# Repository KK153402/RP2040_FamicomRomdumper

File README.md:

# Famicom ROM Dumper rev2（AE-RP2040）

ファミコンカセットを USB 経由で吸い出して `.nes` ファイルに保存するダンパーの、rev2 基板用ファームウェアと PC 側スクリプト。

| 項目 | 内容 |
|---|---|
| 基板 | rev2（MCU：秋月 AE-RP2040、カート電源：TPS2051C）→ [hardware.md](hardware.md) |
| ファーム | v4.4（arduino-pico / PlatformIO） |
| PC スクリプト | `tools/dump_nes.py` v3.1（Python 3、pyserial） |
| プロトコル | [protocol.md](protocol.md) |
| 対応カセット | Mapper 0（NROM）、1（MMC1）、2（UNROM）、3（CNROM）、4（MMC3）は実機確認済み。22（VRC2a）、206（Namco 108 系）は実装のみ（未確認） |
| 実績 | スーパーマリオブラザーズ：CRC32 `D445F698`、Mesen で起動確認 |

## フォルダ構成

| パス | 内容 |
|---|---|
| `platformio.ini` | PlatformIO 設定 |
| `src/main.cpp` | ファームウェア |
| `tools/dump_nes.py` | 吸い出しスクリプト |
| `firmware.uf2` | ビルド済みファーム（ドラッグ＆ドロップ書き込み用） |
| `protocol.md` | シリアルコマンド仕様 |

---

## 1. 開発環境（PlatformIO）

1. VS Code に PlatformIO IDE 拡張を入れる
2. PIO Home → Platforms → Advanced Installation で `https://github.com/maxgerhardt/platform-raspberrypi.git` をインストール
3. このフォルダを開く（初回は toolchain 等のダウンロードに数分かかる）

`platformio.ini`：

```ini
[env:ae-rp2040]
platform = https://github.com/maxgerhardt/platform-raspberrypi.git
board = pico                      ; AE-RP2040 は Pico と同じフラッシュ(2MB)・12MHz 水晶
framework = arduino
board_build.core = earlephilhower ; arduino-pico (Earle Philhower 版)
monitor_speed = 115200            ; USB CDC なので実際の速度とは無関係

; Windows でドライバ不要にするため、RPI-RP2 ドライブへのコピー方式で書き込む
upload_protocol = mbed
upload_port = D:                  ; RPI-RP2 に割り当てられたドライブ文字
```

- `board = rpipico`（「Pico (Raspberry Pi)」）を選んだ場合は `board_build.core` の行は不要
- `platform_packages` でコアのバージョンを古いもの（2.x 等）に固定しないこと（v4.1 以降は 5.x 系で確認）
- Windows でプラットフォームのインストール時に git のエラーが出たら、管理者権限で `git config --system core.longpaths true` を実行してから再インストール

## 2. 書き込み

### 通常（Upload ボタン）

PlatformIO の **Upload（→）** を押す。ファームが動いていれば、1200 bps タッチで自動的に BOOTSEL に入り、`RPI-RP2` ドライブへ `firmware.uf2` がコピーされる。

### 初回・ファームが止まったとき

1. **BOOT を押したまま RUN を押して離し、BOOT を離す** → `RPI-RP2` ドライブが現れる
2. `firmware.uf2`（またはビルド後の `.pio/build/ae-rp2040/firmware.uf2`）を `RPI-RP2` ドライブの中にドラッグ＆ドロップ
3. ドライブが自動で消え、ファームが起動する（「取り外された」等の警告は無視してよい）
4. デバイスマネージャーの「ポート（COM と LPT）」に `USB シリアル デバイス (COMx)` が出れば成功

`RPI-RP2` ドライブは書き込み用の仮想ドライブで、コピーしたファイルは中に残らない（常に `INDEX.HTM` と `INFO_UF2.TXT` だけが見える）。

### 書き込みで出るエラー

| メッセージ | 原因 | 対処 |
|---|---|---|
| `Please specify upload_port` | 書き込み先のドライブが見つからない | `upload_port` に `RPI-RP2` のドライブ文字を指定 |
| `picotool was unable to connect. You may need to install a driver via Zadig` | 既定の picotool 方式は Windows ではドライバが必要 | `upload_protocol = mbed`（上記）にする。または Zadig で **RP2 Boot (Interface 1)** に WinUSB を入れる（**Interface 0 は選ばない**。RPI-RP2 ドライブが見えなくなる） |
| デバイスマネージャーに「RP2 Boot」（！マーク） | BOOTSEL 中の picotool 用インターフェース。ドライバ未導入なだけ | 上と同じ。mbed 方式なら無視してよい |

書き込み中・BOOTSEL 中は GPIO がすべて入力になり、基板のプル抵抗でカート電源 OFF・バス Hi-Z に固定される。カセットを挿したままでも安全。

---

## 3. 動作確認

シリアルモニタ（VS Code の Serial Monitor、Tera Term 等）で行う。ポート欄の ↻ で COM を更新して選ぶ。ボーレートは何でもよい（1200 以外）。

### 3.1 カセットなし

| 操作 | 期待値 | 確認していること |
|---|---|---|
| USB 接続 | D1（+5V）点灯 | 電源 |
| `Q` | `VCC_CART=0〜数十mV  /FLT=1  power=OFF  BUS_EN_N=1` | 起動時の安全状態 |
| `O 1` | `PWR ON vcart=4500〜5100mV`、D2（VCC_CART）・D3（STATUS）点灯 | TPS2051C、VCART_SENSE |
| `T` | 12 行すべて `OK`、最後に `LOOPBACK OK` | データバス 16 本と 595/165/U10 の経路 |
| `R` | `CPU D=FF  PPU D=FF` | プルアップ R1〜R16 |
| `G` | `CIRAM_A10=1  CIRAM_CE_N=1` | プルアップ R33/R34、U11/U12 |
| `O 0` | `PWR OFF vcart=450〜500mV`（警告なし）、D2・D3 消灯 | 放電 |

### 3.2 カセットあり

**カセットの抜き差しは必ず D2（VCC_CART）が消えている状態で行う。** 動作確認が済むまでは USB も抜いておくとより安全。

| 操作 | 期待値（スーパーマリオブラザーズ） | 確認していること |
|---|---|---|
| `O 1` | `PWR ON vcart=4900mV 前後` | カセットの消費電流で極端に下がらないか |
| `V` | `NMI $8082`、`RESET $8000`、`IRQ $FFF0`、3 行とも `[OK]` | PRG 側（CPU アドレス、/ROMSEL、M2） |
| `P FFF0 16` | `FFF0: 19 19 1A 1A 1C 1D 1D 1E 1E 1F 82 80 00 80 F0 FF` | 同上 |
| `H 0000 16` | `0000: 03 0F 1F 1F 1C 24 26 66 00 00 00 00 1F 3F 3F 7F` | CHR 側（PPU アドレス、/RD） |
| `M` | `VERTICAL (follows PA10)` | CIRAM A10 |
| `O 0` | `PWR OFF` | |

`V` が `$FFFF [NG] open bus` のときはカセットが何も出力していない（未挿入・接触不良）。

### 3.3 吸い出し

**シリアルモニタを閉じてから**実行する（COM ポートは 1 つのアプリしか開けない）。

```
python -m pip install pyserial
python tools/dump_nes.py smb.nes
```

出力例（tool v3。`xxxxxxxx` は実測値が入る）：

```
ポート: COM8   マッパー: 0 (NROM)
  PWR ON vcart=4951mV
  [1] PRG 32 KB, CHR 8 KB, mirroring V, CRC32 PRG xxxxxxxx / CHR xxxxxxxx / PRG+CHR D445F698
      所要 1.0 s（うちカセット読み出し 0.9 s）
  [2] PRG 32 KB, CHR 8 KB, mirroring V, CRC32 PRG xxxxxxxx / CHR xxxxxxxx / PRG+CHR D445F698
      所要 1.0 s（うちカセット読み出し 0.9 s）
  2回読み 合計 2.0 s
  PWR OFF vcart=466mV
保存しました: smb.nes
```

- `pip install serial` ではなく **`pyserial`**。仮想環境を使っている場合は `python -m pip` で入れる
- ファーム v4.0 以前（`B` コマンドなし）の場合は `--legacy` を付ける

### 3.4 マッパー付きカセットの吸い出し [tool v3 / fw v4.3]

カセットにはマッパー情報が書かれていないので、**NesCartDB で日本版（日の丸の行）の iNES Mapper を調べて `--mapper` で指定**する。容量（バンク数）と CHR-RAM かどうかは自動で判定する。

```
python tools/dump_nes.py dq2.nes --mapper 2
```

| `--mapper` | マッパー | 主な基板 | 検証用カセット |
|---|---|---|---|
| 0（省略可） | NROM | HVC-NROM | スーパーマリオブラザーズ（確認済み） |
| 1 | MMC1 | HVC-SxROM（SLROM、SGROM、SNROM…） | 忍者龍剣伝（HVC-SLROM） |
| 2 | UNROM | HVC-UNROM、HVC-UOROM | ドラゴンクエストII（HVC-UNROM） |
| 3 | CNROM | HVC-CNROM | ソロモンの鍵（HVC-CNROM） |
| 4 | MMC3 | HVC-TxROM（TLROM、TSROM、TGROM…） | スーパーマリオブラザーズ3（HVC-TSROM） |
| 22 | VRC2a（コナミ） | 351618 など | がんばれペナントレース |
| 206 | Namco 108 系 | NAMCOT-34xx | ドラゴンバスターII |

確認のしかた：

1. 2 回の読み出しが一致して保存されること
2. 表示される `PRG` / `CHR` / `PRG+CHR` の CRC32 が、NesCartDB の ROM Details（PRG0 / CHR0 / ROMs Combined）と一致すること。CHR-RAM のカセットは PRG だけ比べる
3. Mesen で起動すること

CRC32 が合わないときは `--banks` を付けると、PRG は 8 KB、CHR は 1 KB ごとの CRC32 も表示する。版違いか、特定のバンクだけずれているかの切り分けに使う。

| 注意 | 理由 |
|---|---|
| マッパー番号を間違えると `固定バンクと一致するバンクが見つかりません` 等で止まる | 容量判定が成立しないため。保存はされない |
| **バッテリーバックアップ付き（セーブできる）カセットは、セーブデータが消えてもよいものだけにする** | 本ツールは `$6000`〜`$7FFF`（PRG-RAM）には書かないが、抜き差し時の電源の立ち上がり・立ち下がりで消えることがある（実機と同じリスク） |
| MMC1 の PRG 512 KB（SUROM：ドラゴンクエストIV 等）、MMC3 の 4 画面基板は未対応 | バンク切替の追加ビットが必要 |

所要時間の目安（実測の PRG 18.6 µs/B、CHR 35 µs/B から計算。USB 転送とバンク切替の往復を除く）：

| カセット | 容量 | 1 回の読み出し |
|---|---|---|
| ドラゴンクエストII | PRG 128 KB | 約 2.4 s |
| 忍者龍剣伝 | PRG 128 KB + CHR 128 KB | 約 7 s |
| スーパーマリオブラザーズ3 | PRG 256 KB + CHR 128 KB | 約 9.5 s |

---

## 4. 吸い出しがうまくいかないとき

| 症状 | 考えられる原因 | 対処 |
|---|---|---|
| `RP2040 のポートが見つかりません` | ファーム未書き込み、または BOOTSEL のまま | 2. の手順で書き込む |
| `応答がありません` | シリアルモニタが開いたまま | モニタを閉じる |
| `PWR NG` | カセットの短絡・逆挿し、または USB の電源不足 | カセットを確認。USB ハブを使わず PC に直結 |
| `ERR overcurrent` | 吸い出し中に過電流（/FLT） | カセットを抜いて `Q`、`O 1` で再確認 |
| `2回のダンプが一致しません` | カセットの接触不良 | 端子を清掃。それでも NG なら `S 125 1000`（アクセス待ちを延ばす）→ `S 500 1000`（クロックを下げる） |
| `転送エラー` が再送しても直らない | USB ケーブル・ハブ | 別のケーブル、PC の別のポートで試す |

---

## 5. 変更履歴

| 版 | 内容 |
|---|---|
| tool v3.1 | マッパー 22（VRC2a）、206（Namco 108 系）を追加。`--banks`（バンクごとの CRC32 表示）を追加 |
| fw v4.4 | `B P` で `$6000`〜`$7FFF`（PRG-RAM、セーブデータ）を読めるようにした。`$8000` 未満は /ROMSEL を H のまま読む |
| fw v4.3 | MMC1 で書き込みが無視される問題を修正（`W` の前にダミー読み出しサイクルを追加） |
| fw v4.2 / tool v3 | マッパー対応（MMC1 / UNROM / CNROM / MMC3）。CPU 書き込み `W`、PPU 書き込み `X` を追加。容量・CHR-RAM の自動判定、バス競合の回避、PRG / CHR / 合計の CRC32 表示 |
| fw v4.1 / tool v2 | 高速化：SIO 直接操作＋ns 単位のタイミング（シフトクロック 4 MHz）、PRG はアドレス 16 bit・データ 8 bit だけ転送。ブロック読み出し `B`（ブロック CRC、再送）、タイミング設定 `S`（ns 単位）を追加 |
| fw v4.0 / tool v1.2 | Windows で受信データが欠ける問題を修正（`writeAll()`、pySerial の `timeout` を途中で変更しない） |
| fw v4.0 | rev2 初版。v3 を AE-RP2040 に移植。カート電源制御 `O`、状態表示 `Q`、折り返し試験 `T`、過電流監視を追加。電圧を mV 表示に。ベクタ `$FFFF` を NG 判定に |
| v3（rev1） | ESP32 版。ビットバング、115200 bps |

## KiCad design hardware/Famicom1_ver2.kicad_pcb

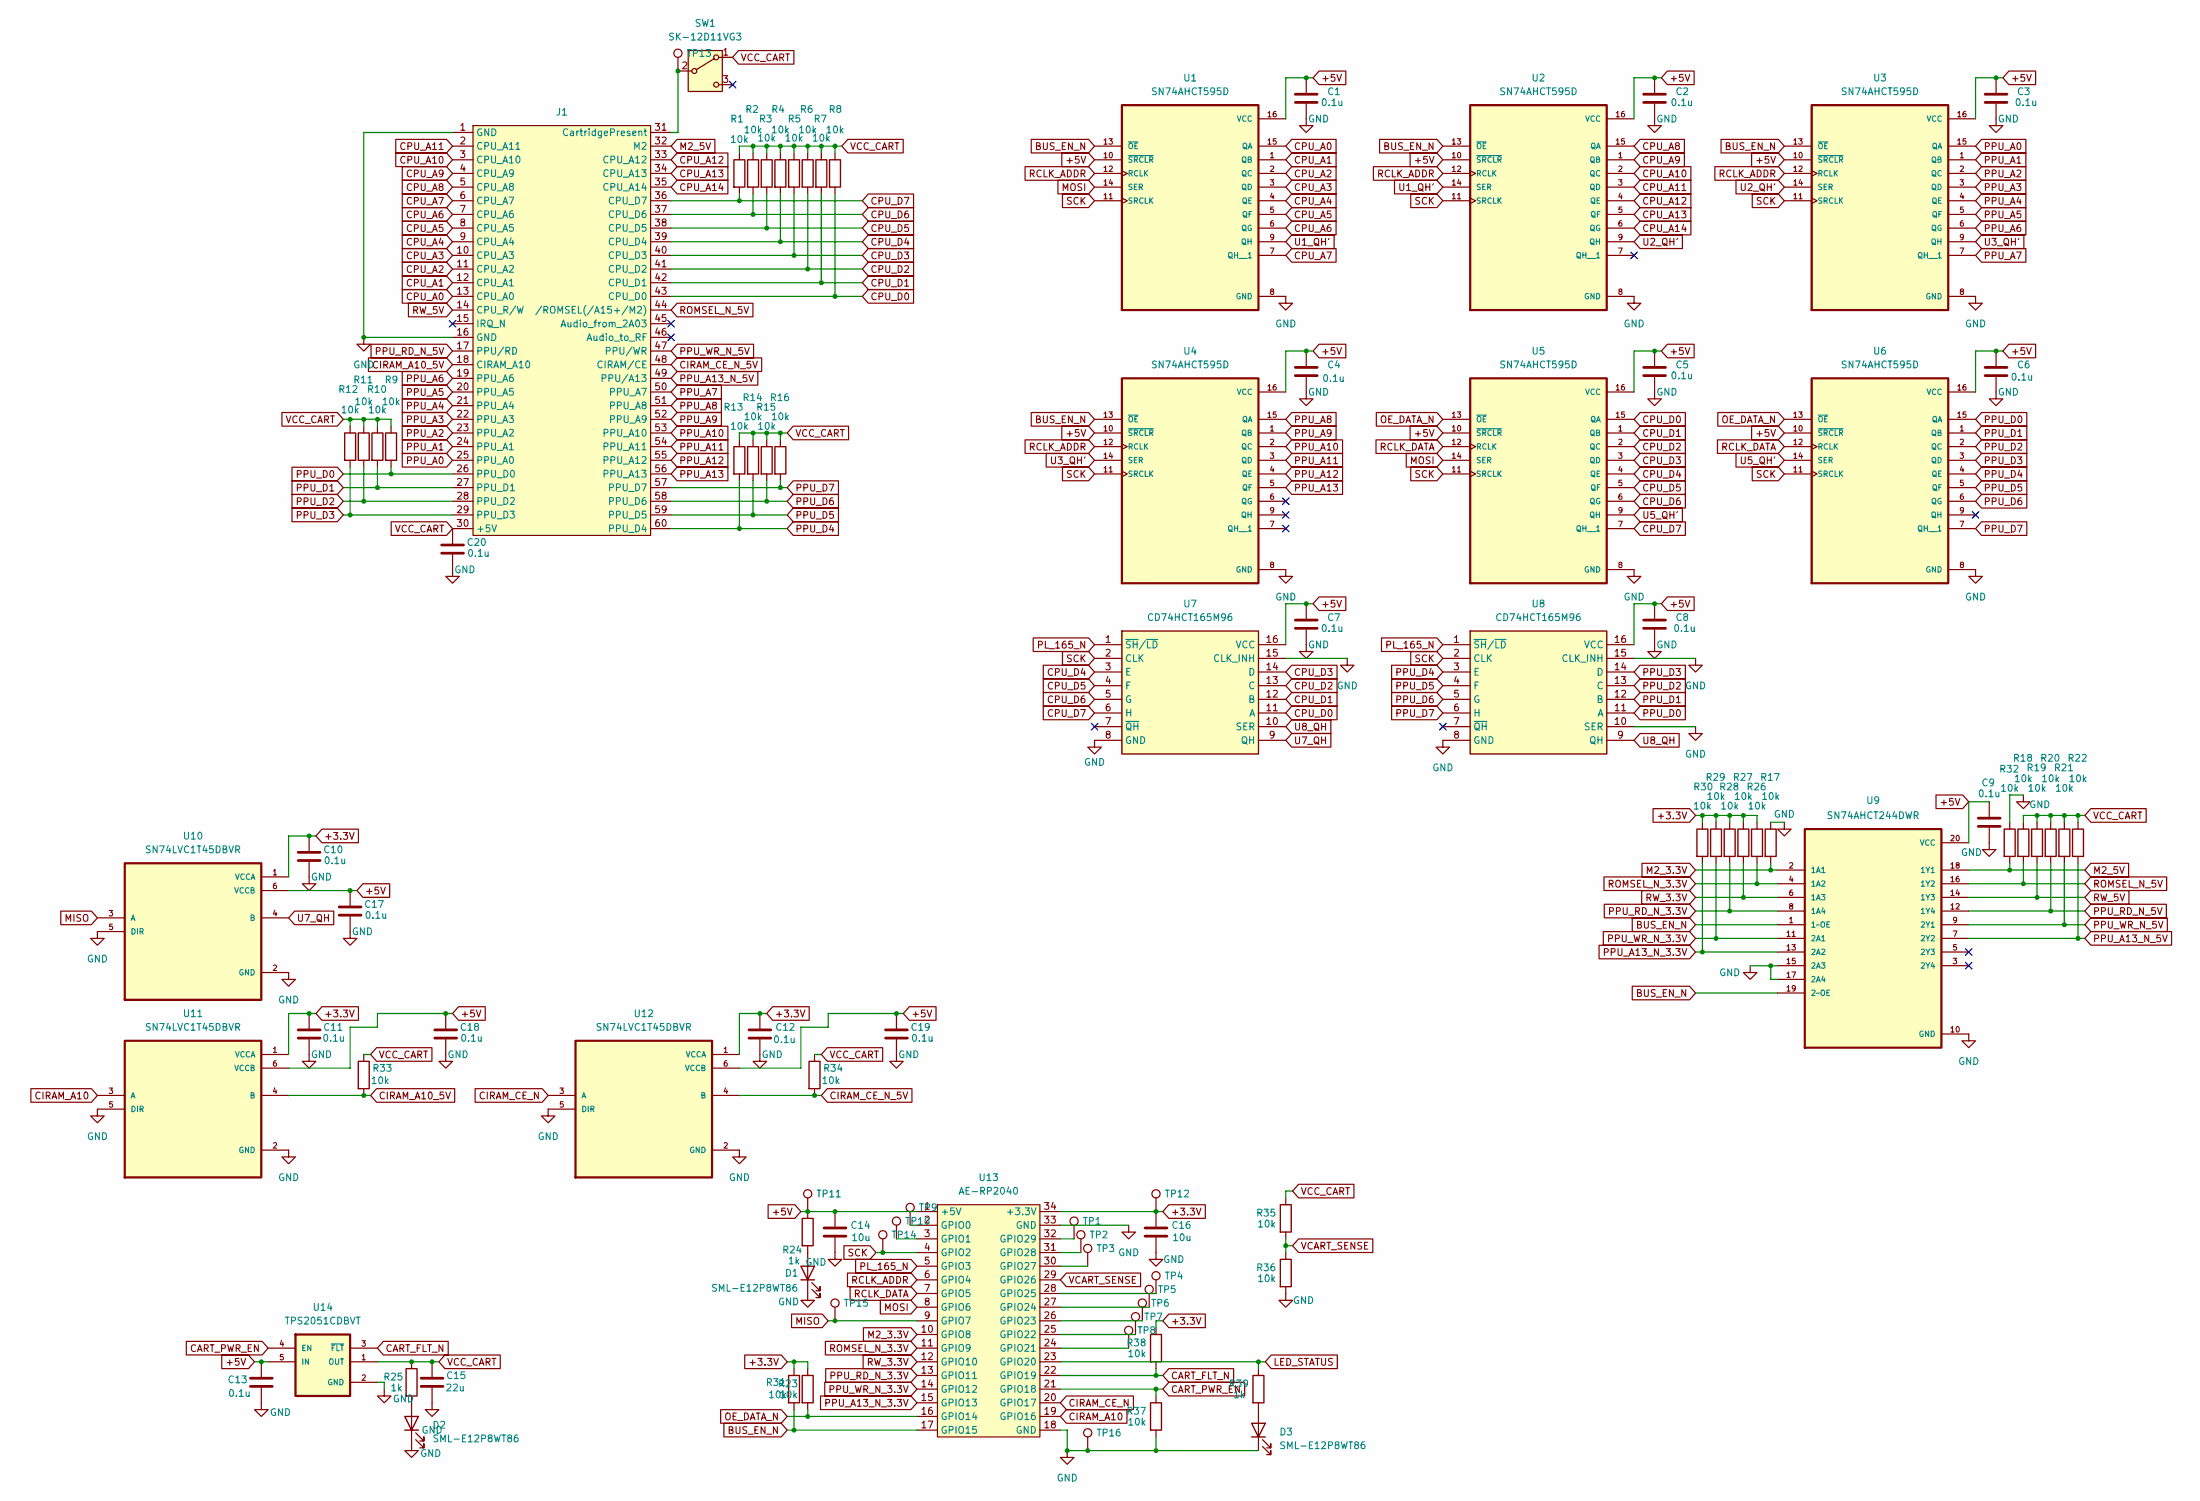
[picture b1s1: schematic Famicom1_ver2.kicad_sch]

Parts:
C1, C2, C3, C4, C5, C6, C7, C8, C9, C10, C11, C12, C13, C17, C18, C19, C20: GRM188F11H104ZA01; C_0603_1608Metric
C14, C16: GRM31CB31H106KA12; C_1206_3216Metric
C15: GRM32EB31E226KE15; C_1210_3225Metric
D1, D2, D3: SML-E12P8WT86
J1: FamilyComputer_60pin
R1, R2, R3, R4, R5, R6, R7, R8, R9, R10, R11, R12, R13, R14, R15, R16, R17, R18, R19, R20, R21, R22, R23, R26, R27, R28, R29, R30, R31, R32, R33, R34, R35, R36, R37, R38: RK73B1JTTD103J; R_0603_1608Metric
R24, R25, R39: RK73B1JTTD102J; R_0603_1608Metric
SW1: SK-12D11VG3
TP1, TP2, TP3, TP4, TP5, TP6, TP7, TP8, TP9, TP10, TP11, TP12, TP13, TP14, TP15, TP16: TestPoint; TestPoint_Pad_1.5x1.5mm
U1, U2, U3, U4, U5, U6: SN74AHCT595D
U7, U8: CD74HCT165M96; Manufacturer_Part_Number CD74HCT165M96; Mouser Part Number 595-CD74HCT165M96
U9: SN74AHCT244DWR
U10, U11, U12: SN74LVC1T45DBVR
U13: AE-RP2040
U14: TPS2051CDBVT

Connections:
+3.3V: C10.1, C11.1, C12.1, C16.1, R23.1, R26.1, R27.1, R28.1, R29.1, R30.1, R31.1, R38.1, TP12.1 (1_1), U10.1 (VCCA), U11.1 (VCCA), U12.1 (VCCA), U13.34 (+3.3V)
+5V: C1.1, C2.1, C3.1, C4.1, C5.1, C6.1, C7.1, C8.1, C9.1, C13.1, C14.1, C17.1, C18.1, C19.1, R24.1, TP11.1 (1_1), U1.10 (~SRCLR), U1.16 (VCC), U2.10 (~SRCLR), U2.16 (VCC), U3.10 (~SRCLR), U3.16 (VCC), U4.10 (~SRCLR), U4.16 (VCC), U5.10 (~SRCLR), U5.16 (VCC), U6.10 (~SRCLR), U6.16 (VCC), U7.16 (VCC), U8.16 (VCC), U9.20 (VCC), U10.6 (VCCB), U11.6 (VCCB), U12.6 (VCCB), U13.1 (+5V), U14.5 (IN)
BUS_EN_N: R31.2, U1.13 (~OE), U2.13 (~OE), U3.13 (~OE), U4.13 (~OE), U9.1 (1~OE), U9.19 (2~OE), U13.17 (GPIO15)
CART_FLT_N: R38.2, U13.22 (GPIO19), U14.3 (~FLT)
CART_PWR_EN: R37.1, U13.21 (GPIO18), U14.4 (EN)
CIRAM_A10: U11.3 (A), U13.19 (GPIO16)
CIRAM_A10_5V: J1.18 (CIRAM_A10), R33.2, U11.4 (B)
CIRAM_CE_N: U12.3 (A), U13.20 (GPIO17)
CIRAM_CE_N_5V: J1.48 (CIRAM/CE), R34.2, U12.4 (B)
CPU_A0: J1.13 (CPU_A0), U1.15 (QA)
CPU_A1: J1.12 (CPU_A1), U1.1 (QB)
CPU_A2: J1.11 (CPU_A2), U1.2 (QC)
CPU_A3: J1.10 (CPU_A3), U1.3 (QD)
CPU_A4: J1.9 (CPU_A4), U1.4 (QE)
CPU_A5: J1.8 (CPU_A5), U1.5 (QF)
CPU_A6: J1.7 (CPU_A6), U1.6 (QG)
CPU_A7: J1.6 (CPU_A7), U1.7 (QH__1)
CPU_A8: J1.5 (CPU_A8), U2.15 (QA)
CPU_A9: J1.4 (CPU_A9), U2.1 (QB)
CPU_A10: J1.3 (CPU_A10), U2.2 (QC)
CPU_A11: J1.2 (CPU_A11), U2.3 (QD)
CPU_A12: J1.33 (CPU_A12), U2.4 (QE)
CPU_A13: J1.34 (CPU_A13), U2.5 (QF)
CPU_A14: J1.35 (CPU_A14), U2.6 (QG)
CPU_D0: J1.43 (CPU_D0), R8.2, U5.15 (QA), U7.11 (A)
CPU_D1: J1.42 (CPU_D1), R7.2, U5.1 (QB), U7.12 (B)
CPU_D2: J1.41 (CPU_D2), R6.2, U5.2 (QC), U7.13 (C)
CPU_D3: J1.40 (CPU_D3), R5.2, U5.3 (QD), U7.14 (D)
CPU_D4: J1.39 (CPU_D4), R4.2, U5.4 (QE), U7.3 (E)
CPU_D5: J1.38 (CPU_D5), R3.2, U5.5 (QF), U7.4 (F)
CPU_D6: J1.37 (CPU_D6), R2.2, U5.6 (QG), U7.5 (G)
CPU_D7: J1.36 (CPU_D7), R1.2, U5.7 (QH__1), U7.6 (H)
GND: C1.2, C2.2, C3.2, C4.2, C5.2, C6.2, C7.2, C8.2, C9.2, C10.2, C11.2, C12.2, C13.2, C14.2, C15.2, C16.2, C17.2, C18.2, C19.2, C20.2, D1.1 (K), D2.1 (K), D3.1 (K), J1.1 (GND), J1.16 (GND), R17.1, R32.1, R36.2, R37.2, TP16.1 (1_1), U1.8 (GND), U2.8 (GND), U3.8 (GND), U4.8 (GND), U5.8 (GND), U6.8 (GND), U7.8 (GND), U7.15 (CLK_INH), U8.8 (GND), U8.10 (SER), U8.15 (CLK_INH), U9.10 (GND), U9.15 (2A3), U9.17 (2A4), U10.2 (GND), U10.5 (DIR), U11.2 (GND), U11.5 (DIR), U12.2 (GND), U12.5 (DIR), U13.18 (GND), U13.33 (GND), U14.2 (GND)
LED_STATUS: R39.1, U13.23 (GPIO20)
M2_3.3V: R17.2, U9.2 (1A1), U13.10 (GPIO8)
M2_5V: J1.32 (M2), R32.2, U9.18 (1Y1)
MISO: TP15.1 (1_1), U10.3 (A), U13.9 (GPIO7)
MOSI: U1.14 (SER), U5.14 (SER), U13.8 (GPIO6)
unnamed: D1.2 (A), R24.2
unnamed: D2.2 (A), R25.2
unnamed: D3.2 (A), R39.2
unnamed: J1.31 (CartridgePresent), SW1.2 (B), TP13.1 (1_1)
unnamed: TP9.1 (1_1), U13.2 (GPIO0)
unnamed: TP10.1 (1_1), U13.3 (GPIO1)
unnamed: TP8.1 (1_1), U13.24 (GPIO21)
unnamed: TP7.1 (1_1), U13.25 (GPIO22)
unnamed: TP6.1 (1_1), U13.26 (GPIO23)
unnamed: TP5.1 (1_1), U13.27 (GPIO24)
unnamed: TP4.1 (1_1), U13.28 (GPIO25)
unnamed: TP3.1 (1_1), U13.30 (GPIO27)
unnamed: TP2.1 (1_1), U13.31 (GPIO28)
unnamed: TP1.1 (1_1), U13.32 (GPIO29)
OE_DATA_N: R23.2, U5.13 (~OE), U6.13 (~OE), U13.16 (GPIO14)
PL_165_N: U7.1 (~SH/~LD), U8.1 (~SH/~LD), U13.5 (GPIO3)
PPU_A0: J1.25 (PPU_A0), U3.15 (QA)
PPU_A1: J1.24 (PPU_A1), U3.1 (QB)
PPU_A2: J1.23 (PPU_A2), U3.2 (QC)
PPU_A3: J1.22 (PPU_A3), U3.3 (QD)
PPU_A4: J1.21 (PPU_A4), U3.4 (QE)
PPU_A5: J1.20 (PPU_A5), U3.5 (QF)
PPU_A6: J1.19 (PPU_A6), U3.6 (QG)
PPU_A7: J1.50 (PPU_A7), U3.7 (QH__1)
PPU_A8: J1.51 (PPU_A8), U4.15 (QA)
PPU_A9: J1.52 (PPU_A9), U4.1 (QB)
PPU_A10: J1.53 (PPU_A10), U4.2 (QC)
PPU_A11: J1.54 (PPU_A11), U4.3 (QD)
PPU_A12: J1.55 (PPU_A12), U4.4 (QE)
PPU_A13: J1.56 (PPU_A13), U4.5 (QF)
PPU_A13_N_3.3V: R30.2, U9.13 (2A2), U13.15 (GPIO13)
PPU_A13_N_5V: J1.49 (PPU/A13), R22.2, U9.7 (2Y2)
PPU_D0: J1.26 (PPU_D0), R9.2, U6.15 (QA), U8.11 (A)
PPU_D1: J1.27 (PPU_D1), R10.2, U6.1 (QB), U8.12 (B)
PPU_D2: J1.28 (PPU_D2), R11.2, U6.2 (QC), U8.13 (C)
PPU_D3: J1.29 (PPU_D3), R12.2, U6.3 (QD), U8.14 (D)
PPU_D4: J1.60 (PPU_D4), R13.2, U6.4 (QE), U8.3 (E)
PPU_D5: J1.59 (PPU_D5), R14.2, U6.5 (QF), U8.4 (F)
PPU_D6: J1.58 (PPU_D6), R15.2, U6.6 (QG), U8.5 (G)
PPU_D7: J1.57 (PPU_D7), R16.2, U6.7 (QH__1), U8.6 (H)
PPU_RD_N_3.3V: R28.2, U9.8 (1A4), U13.13 (GPIO11)
PPU_RD_N_5V: J1.17 (PPU/RD), R20.2, U9.12 (1Y4)
PPU_WR_N_3.3V: R29.2, U9.11 (2A1), U13.14 (GPIO12)
PPU_WR_N_5V: J1.47 (PPU/WR), R21.2, U9.9 (2Y1)
RCLK_ADDR: U1.12 (RCLK), U2.12 (RCLK), U3.12 (RCLK), U4.12 (RCLK), U13.6 (GPIO4)
RCLK_DATA: U5.12 (RCLK), U6.12 (RCLK), U13.7 (GPIO5)
ROMSEL_N_3.3V: R26.2, U9.4 (1A2), U13.11 (GPIO9)
ROMSEL_N_5V: J1.44 (/ROMSEL(/A15+/M2)), R18.2, U9.16 (1Y2)
RW_3.3V: R27.2, U9.6 (1A3), U13.12 (GPIO10)
RW_5V: J1.14 (CPU_R/W), R19.2, U9.14 (1Y3)
SCK: TP14.1 (1_1), U1.11 (SRCLK), U2.11 (SRCLK), U3.11 (SRCLK), U4.11 (SRCLK), U5.11 (SRCLK), U6.11 (SRCLK), U7.2 (CLK), U8.2 (CLK), U13.4 (GPIO2)
U1_QH': U1.9 (QH), U2.14 (SER)
U2_QH': U2.9 (QH), U3.14 (SER)
U3_QH': U3.9 (QH), U4.14 (SER)
U5_QH': U5.9 (QH), U6.14 (SER)
U7_QH: U7.9 (QH), U10.4 (B)
U8_QH: U7.10 (SER), U8.9 (QH)
VCART_SENSE: R35.2, R36.1, U13.29 (GPIO26)
VCC_CART: C15.1, C20.1, J1.30 (+5V), R1.1, R2.1, R3.1, R4.1, R5.1, R6.1, R7.1, R8.1, R9.1, R10.1, R11.1, R12.1, R13.1, R14.1, R15.1, R16.1, R18.1, R19.1, R20.1, R21.1, R22.1, R25.1, R33.1, R34.1, R35.1, SW1.1 (A), U14.1 (OUT)

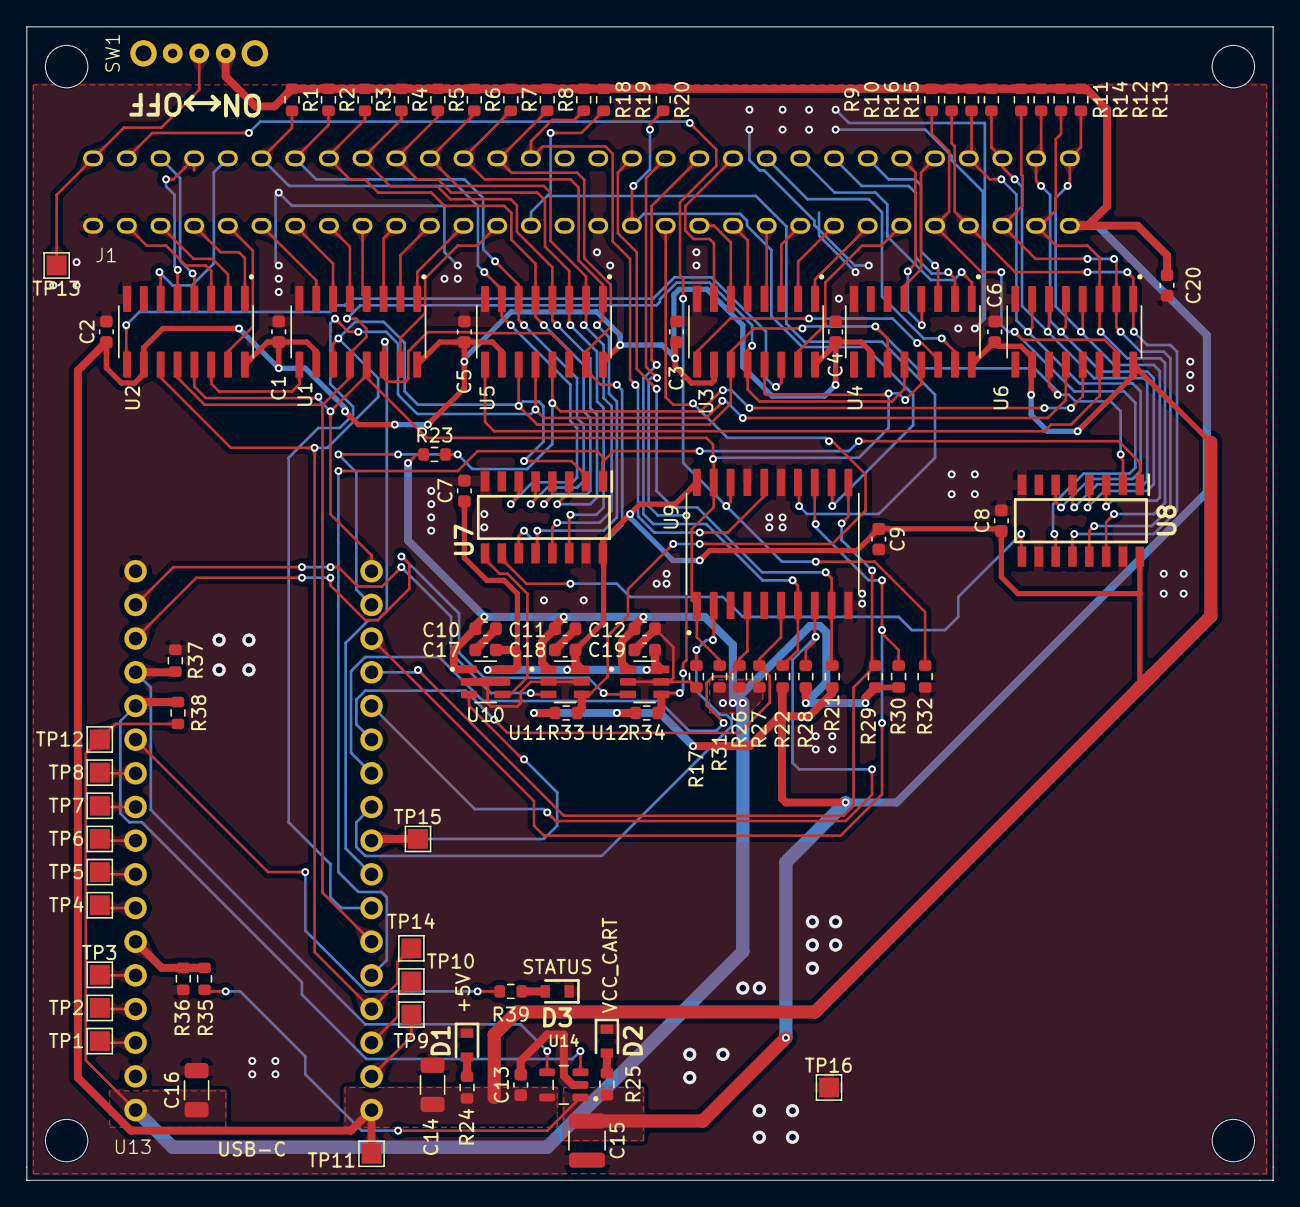
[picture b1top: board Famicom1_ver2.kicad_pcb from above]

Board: 2 copper layers, 94.0 x 87.0 mm, 94 parts (0 on the bottom side), 97 nets.

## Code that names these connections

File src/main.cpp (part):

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
// ---- ピン割り当て（hardware.md §5.2）----
constexpr uint PIN_SCK       = 2;
constexpr uint PIN_PL_165_N  = 3;
constexpr uint PIN_RCLK_ADDR = 4;
constexpr uint PIN_RCLK_DATA = 5;
constexpr uint PIN_MOSI      = 6;
constexpr uint PIN_MISO      = 7;
constexpr uint PIN_M2        = 8;
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constexpr uint PIN_PPU_RD_N  = 11;
constexpr uint PIN_PPU_WR_N  = 12;
constexpr uint PIN_PPU_A13_N = 13;
constexpr uint PIN_OE_DATA_N = 14;
constexpr uint PIN_BUS_EN_N  = 15;
constexpr uint PIN_CIRAM_A10 = 16;
constexpr uint PIN_CIRAM_CE_N= 17;
constexpr uint PIN_CART_PWR_EN = 18;
constexpr uint PIN_CART_FLT_N  = 19;
constexpr uint PIN_STATUS_LED       = 20;
constexpr uint PIN_VCART_SENSE = 26;   // ADC0

// ---- 電源判定しきい値（hardware.md §6.5 / §9.5）----
constexpr float VCART_ON_MIN  = 4.0f;  // ON 判定 (ADC 2.0 V)
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
float readVcart() {                    // R35/R36 = 1/2 分圧
  uint32_t s = 0;
  for (int i = 0; i < 8; i++) s += analogRead(PIN_VCART_SENSE);
  return (s / 8.0f) * 3.3f / 4095.0f * 2.0f;
}

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static inline void pulse(uint p) { hi(p); waitCyc(clkCyc); lo(p); }

static inline void loadPL() {          // 165 にパラレルロード
  lo(PIN_PL_165_N);
  waitCyc(clkCyc);                     // tw(SH/LD) ≥ 25 ns
  hi(PIN_PL_165_N);
  waitCyc(clkCyc);                     // tREC ≥ 25 ns, tpd(SH/LD→QH) ≤ 40 ns
}

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void setAddr(uint16_t cpuA, uint16_t ppuA) {
  uint32_t w = ((uint32_t)(ppuA & 0x3FFF) << 16) | (cpuA & 0x7FFF);
  shiftOutBits(w, 32);
  pulse(PIN_RCLK_ADDR);
}

// 165 に現在のバス値をロードして 16bit 読む。上位 = CPU D, 下位 = PPU D
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// v4.4: $6000-$7FFF（PRG-RAM）も読める。$8000 未満は /ROMSEL を H のまま（M2 = H、R/W = H の読み出しサイクル）
uint8_t __not_in_flash_func(readPrg)(uint16_t addr) {   // addr: $6000-$FFFF
  shiftOutBits(addr & 0x7FFF, 16);
  pulse(PIN_RCLK_ADDR);
  hi(PIN_RW);
  hi(PIN_M2);
  if (addr & 0x8000) lo(PIN_ROMSEL_N);
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
// ---- カート電源（hardware.md §9.5）---------------------------------
void cartOff() {
  put(PIN_OE_DATA_N, 1);
  idleBus();
  put(PIN_BUS_EN_N, 1);
  put(PIN_CART_PWR_EN, 0);
  cartPower = false;
  uint32_t t0 = millis();
  float v;
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}

bool cartOn() {
  put(PIN_OE_DATA_N, 1);
  idleBus();
  put(PIN_BUS_EN_N, 1);
  put(PIN_CART_PWR_EN, 1);
  delay(10);                           // tON 1.8ms + tR 0.7ms (max) に余裕
  float v = readVcart();
  bool flt = !get(PIN_CART_FLT_N);
  if (flt || v < VCART_ON_MIN) {
    put(PIN_CART_PWR_EN, 0);
    cartPower = false;
    Serial.printf("PWR NG vcart=%dmV flt=%d\n", mV(v), flt);
    return false;
  }
  put(PIN_BUS_EN_N, 0);
  cartPower = true;
  put(PIN_STATUS_LED, 1);
  Serial.printf("PWR ON vcart=%dmV\n", mV(v));
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
// 動作中の過電流監視。/FLT が出ていたら即遮断して false
bool faultCheck() {
  if (cartPower && !get(PIN_CART_FLT_N)) {
    put(PIN_OE_DATA_N, 1);
    put(PIN_BUS_EN_N, 1);
    put(PIN_CART_PWR_EN, 0);
    cartPower = false;
    put(PIN_STATUS_LED, 0);
    Serial.println("ERR overcurrent (/FLT) - cart power cut");
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void loadData(uint8_t cpuD, uint8_t ppuD) {
  shiftOutByte(ppuD);                  // 先に送った方が U6 (PPU D) に入る
  shiftOutByte(cpuD);                  // U5 (CPU D)
  pulse(PIN_RCLK_DATA);
}

void cmdLoopback() {
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  for (uint8_t p : pat) {
    uint8_t q = (uint8_t)~p;           // PPU 側は反転パターン（CPU/PPU 間の短絡も検出）
    loadData(p, q);
    put(PIN_OE_DATA_N, 0);
    delayMicroseconds(2);
    uint16_t r = read165();
    put(PIN_OE_DATA_N, 1);
    uint8_t rc = r >> 8, rp = r & 0xFF;
    badCpu |= rc ^ p; badPpu |= rp ^ q;
    Serial.printf("write CPU=%02X PPU=%02X  read CPU=%02X PPU=%02X %s\n", p, q, rc, rp,
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  idleBus();
  loadData(d, 0xFF);
  shiftOutBits(addr & 0x7FFF, 16);
  pulse(PIN_RCLK_ADDR);
  hi(PIN_M2);                 // ダミー読み出し（/ROMSEL=H なので ROM は出力しない）
  waitCyc(accCyc);
  lo(PIN_M2);
  waitCyc(clkCyc);
  lo(PIN_RW);
  waitCyc(clkCyc);
  lo(PIN_OE_DATA_N);
  hi(PIN_M2);
  if (addr & 0x8000) lo(PIN_ROMSEL_N);
  waitCyc(accCyc);
  hi(PIN_ROMSEL_N);
  lo(PIN_M2);
  waitCyc(clkCyc);
  hi(PIN_OE_DATA_N);
  waitCyc(clkCyc);
  hi(PIN_RW);
}
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  idleBus();
  loadData(0xFF, d);
  setAddr(0x0000, addr & 0x1FFF);      // PA13 = 0, /A13 = 1
  lo(PIN_OE_DATA_N);
  waitCyc(clkCyc);
  lo(PIN_PPU_WR_N);
  waitCyc(accCyc);
  hi(PIN_PPU_WR_N);
  waitCyc(clkCyc);
  hi(PIN_OE_DATA_N);
}

// ---------------------------------------------------------------
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
char detectMirror(int* base, int* a10, int* a11) {   // 'V' / 'H' / '?'
  // CIRAM A10 はカセット内の配線（または マッパー）経由で返ってくるので、ラッチ後に少し待って読む
  setAddr(0, 0x2000);          delayMicroseconds(1); *base = get(PIN_CIRAM_A10);
  setAddr(0, 0x2000 | 0x0400); delayMicroseconds(1); *a10  = get(PIN_CIRAM_A10);   // PA10=1
  setAddr(0, 0x2000 | 0x0800); delayMicroseconds(1); *a11  = get(PIN_CIRAM_A10);   // PA11=1
  if (*base == 0 && *a10 == 1 && *a11 == 0) return 'V';
  if (*base == 0 && *a10 == 0 && *a11 == 1) return 'H';
  return '?';
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    case 'O': if (a1.toInt()) cartOn(); else cartOff(); break;
    case 'Q':
      Serial.printf("VCC_CART=%dmV  /FLT=%d  power=%s  BUS_EN_N=%d\n", mV(readVcart()),
                    get(PIN_CART_FLT_N), cartPower ? "ON" : "OFF", get(PIN_BUS_EN_N));
      break;
    case 'E':
      if (!a1.toInt() && !cartPower) {
        Serial.println("WARN: cart power is OFF. BUS_EN_N=0 drives an unpowered cart.");
      }
      put(PIN_BUS_EN_N, a1.toInt() ? 1 : 0);
      Serial.printf("BUS_EN_N = %d (%s)\n", (int)a1.toInt() ? 1 : 0, a1.toInt() ? "Hi-Z" : "enabled");
      break;
    case 'A':
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    case 'R': { uint16_t v = read165();
      Serial.printf("CPU D=%02X  PPU D=%02X\n", v >> 8, v & 0xFF); } break;
    case 'G':
      Serial.printf("CIRAM_A10=%d  CIRAM_CE_N=%d\n", get(PIN_CIRAM_A10), get(PIN_CIRAM_CE_N));
      break;
    case 'T': cmdLoopback(); break;
    case 'S':
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// ---------------------------------------------------------------
void setup() {
  // 安全側の値を書いてから出力にする（リセット中は基板のプル抵抗で同じ状態）
  outInit(PIN_CART_PWR_EN, 0);         // カート電源 OFF
  outInit(PIN_BUS_EN_N, 1);            // U1-U4, U9 Hi-Z
  outInit(PIN_OE_DATA_N, 1);           // U5-U6 Hi-Z
  outInit(PIN_M2, 0);
  outInit(PIN_ROMSEL_N, 1);
  outInit(PIN_RW, 1);
  outInit(PIN_PPU_RD_N, 1);
  outInit(PIN_PPU_WR_N, 1);
  outInit(PIN_PPU_A13_N, 1);
  outInit(PIN_PL_165_N, 1);
  outInit(PIN_RCLK_ADDR, 0);
  outInit(PIN_RCLK_DATA, 0);
  outInit(PIN_SCK, 0);
  outInit(PIN_MOSI, 0);
  outInit(PIN_STATUS_LED, 0);
  const uint inputs[] = {PIN_MISO, PIN_CIRAM_A10, PIN_CIRAM_CE_N, PIN_CART_FLT_N};
  for (uint p : inputs) {
    gpio_init(p);                      // 入力。プルは基板側にあるので内部プルは無効
    gpio_disable_pulls(p);
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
